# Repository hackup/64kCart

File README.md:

# 64kCart

The 64kCart is a simple bank switching cartridge for the C64/C128. It is a remake of the ["64k-Karte"](http://www.idealine.info/emuecke/index_quereinstieg.htm?/emuecke/hardware/64k_modulkart.htm) created by Hucky which supports EPROM types 2764 up to 27512.

There is also no warranty whatsoever. **USE AT YOUR OWN RISK!**.

See my [blog post](https://www.hackup.net/2019/07/bank-switching-cartridges/) for more details.

## License
[
](http://creativecommons.org/licenses/by-nc-sa/4.0/)

This work is licensed under a
[Creative Commons Attribution-NonCommercial-ShareAlike 4.0 International License](http://creativecommons.org/licenses/by-nc-sa/4.0/).

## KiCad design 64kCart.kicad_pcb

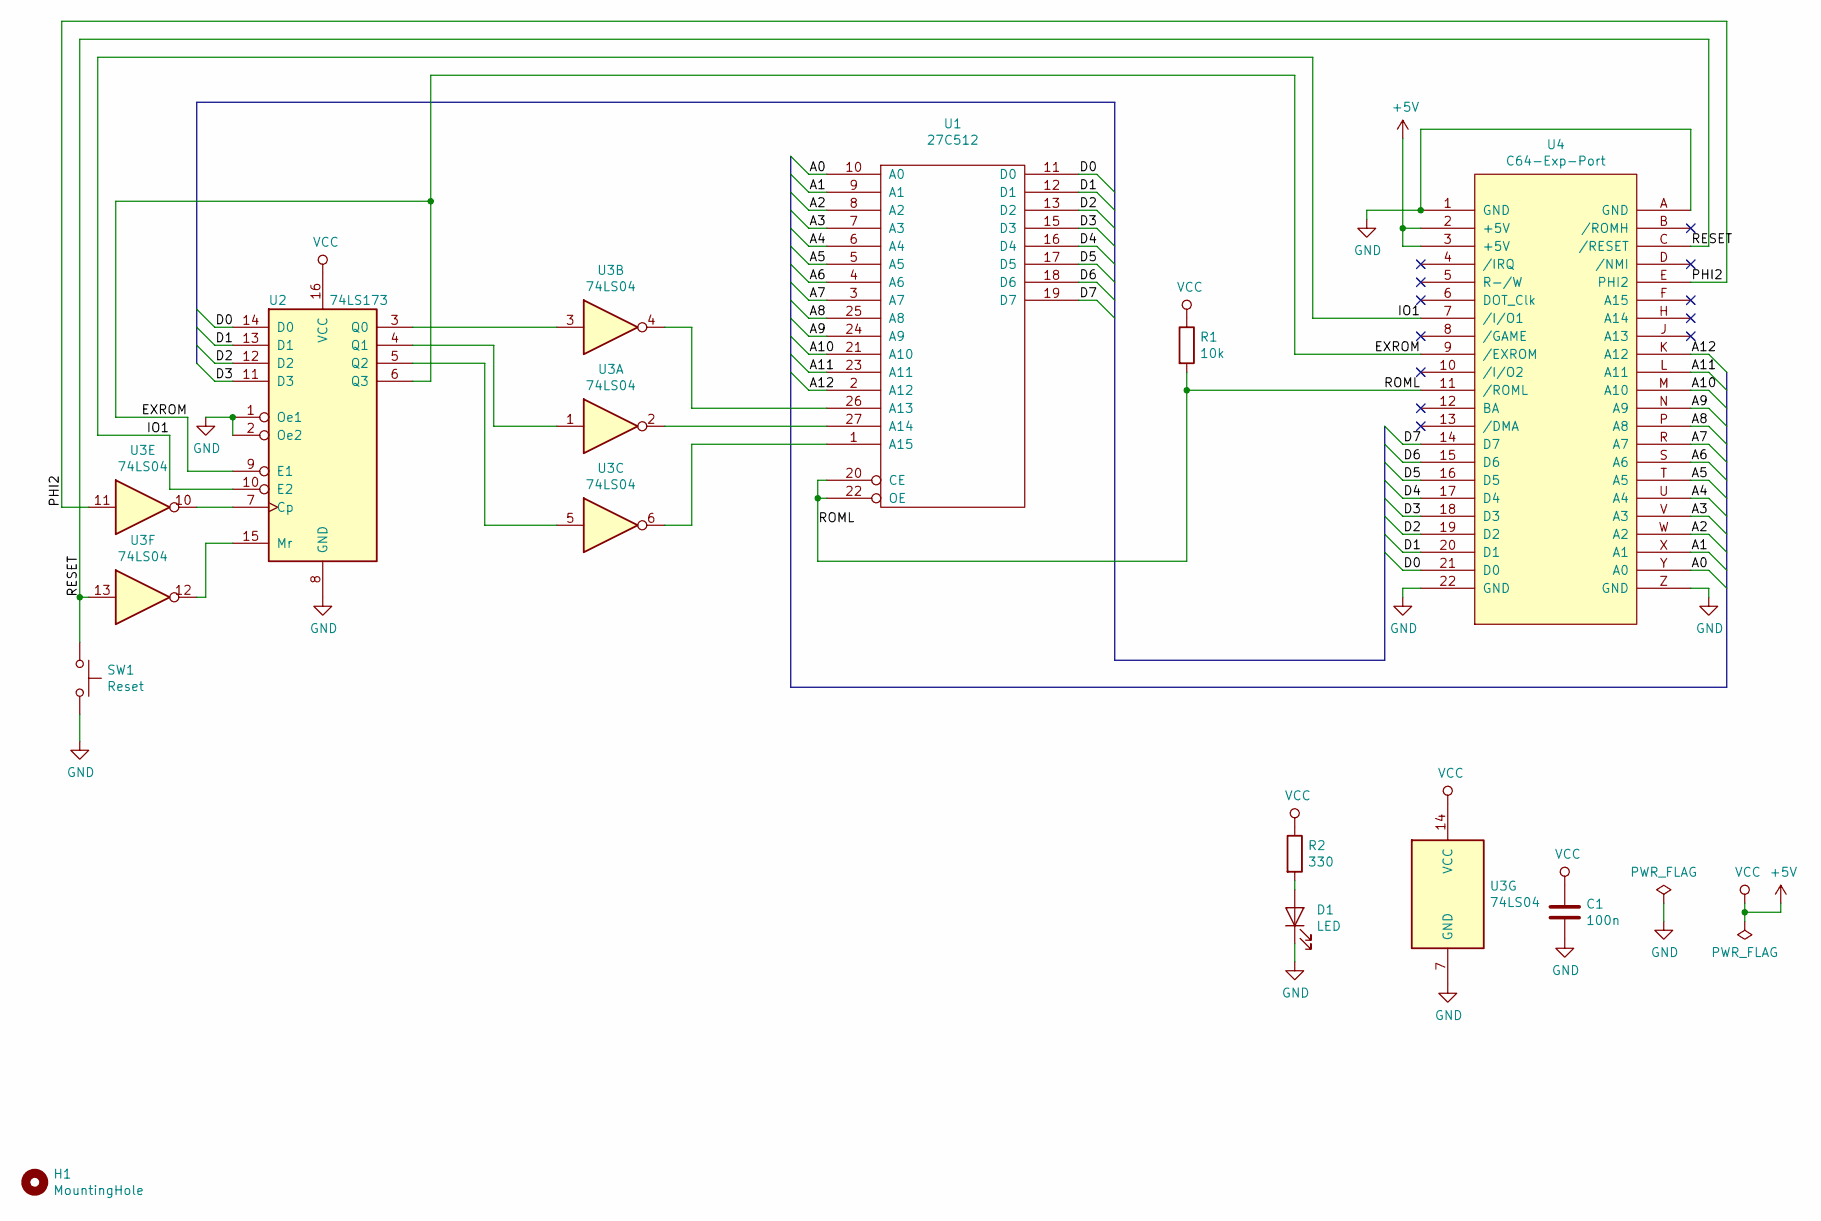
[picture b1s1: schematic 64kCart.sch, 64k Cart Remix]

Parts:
C1: 100n; C_Disc_D4.3mm_W1.9mm_P5.00mm
D1: LED; LED_D3.0mm
H1: MountingHole; MountingHole_CartCombined
R1: 10k; R_Axial_DIN0207_L6.3mm_D2.5mm_P7.62mm_Horizontal
R2: 330; R_Axial_DIN0207_L6.3mm_D2.5mm_P7.62mm_Horizontal
SW1: Reset; SW_Tactile_SPST_Angled_PTS645Vx83-2LFS
U1: 27C512; DIP-28_W15.24mm_Socket
U2: 74LS173; DIP-16_W7.62mm_Socket
U3: 74LS04; DIP-14_W7.62mm_Socket
U4: C64-Exp-Port; C64-Cart-NoSilkS

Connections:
+5V: C1.1, R1.1, R2.1, U1.28 (VCC), U2.16 (VCC), U3.14 (VCC), U4.2 (+5V), U4.3 (+5V)
/A0: U1.10 (A0), U4.Y (A0)
/A1: U1.9 (A1), U4.X (A1)
/A2: U1.8 (A2), U4.W (A2)
/A3: U1.7 (A3), U4.V (A3)
/A4: U1.6 (A4), U4.U (A4)
/A5: U1.5 (A5), U4.T (A5)
/A6: U1.4 (A6), U4.S (A6)
/A7: U1.3 (A7), U4.R (A7)
/A8: U1.25 (A8), U4.P (A8)
/A9: U1.24 (A9), U4.N (A9)
/A10: U1.21 (A10), U4.M (A10)
/A11: U1.23 (A11), U4.L (A11)
/A12: U1.2 (A12), U4.K (A12)
/D0: U1.11 (D0), U2.14 (D0), U4.21 (D0)
/D1: U1.12 (D1), U2.13 (D1), U4.20 (D1)
/D2: U1.13 (D2), U2.12 (D2), U4.19 (D2)
/D3: U1.15 (D3), U2.11 (D3), U4.18 (D3)
/D4: U1.16 (D4), U4.17 (D4)
/D5: U1.17 (D5), U4.16 (D5)
/D6: U1.18 (D6), U4.15 (D6)
/D7: U1.19 (D7), U4.14 (D7)
/EXROM: U2.6 (Q3), U2.9 (E1), U4.9 (/EXROM)
/IO1: U2.10 (E2), U4.7 (/I/O1)
/PHI2: U3.11, U4.E (PHI2)
/RESET: SW1.1, U3.13, U4.C (/RESET)
/ROML: R1.2, U1.20 (CE), U1.22 (OE), U4.11 (/ROML)
GND: C1.2, D1.1 (K), SW1.2, U1.14 (GND), U2.1 (Oe1), U2.2 (Oe2), U2.8 (GND), U3.7 (GND), U4.1 (GND), U4.22 (GND), U4.A (GND), U4.Z (GND)
unnamed: D1.2 (A), R2.2
unnamed: U1.1 (A15), U3.6
unnamed: U1.26 (A13), U3.4
unnamed: U1.27 (A14), U3.2
unnamed: U2.3 (Q0), U3.3
unnamed: U2.4 (Q1), U3.1
unnamed: U2.5 (Q2), U3.5
unnamed: U2.7 (Cp), U3.10
unnamed: U2.15 (Mr), U3.12

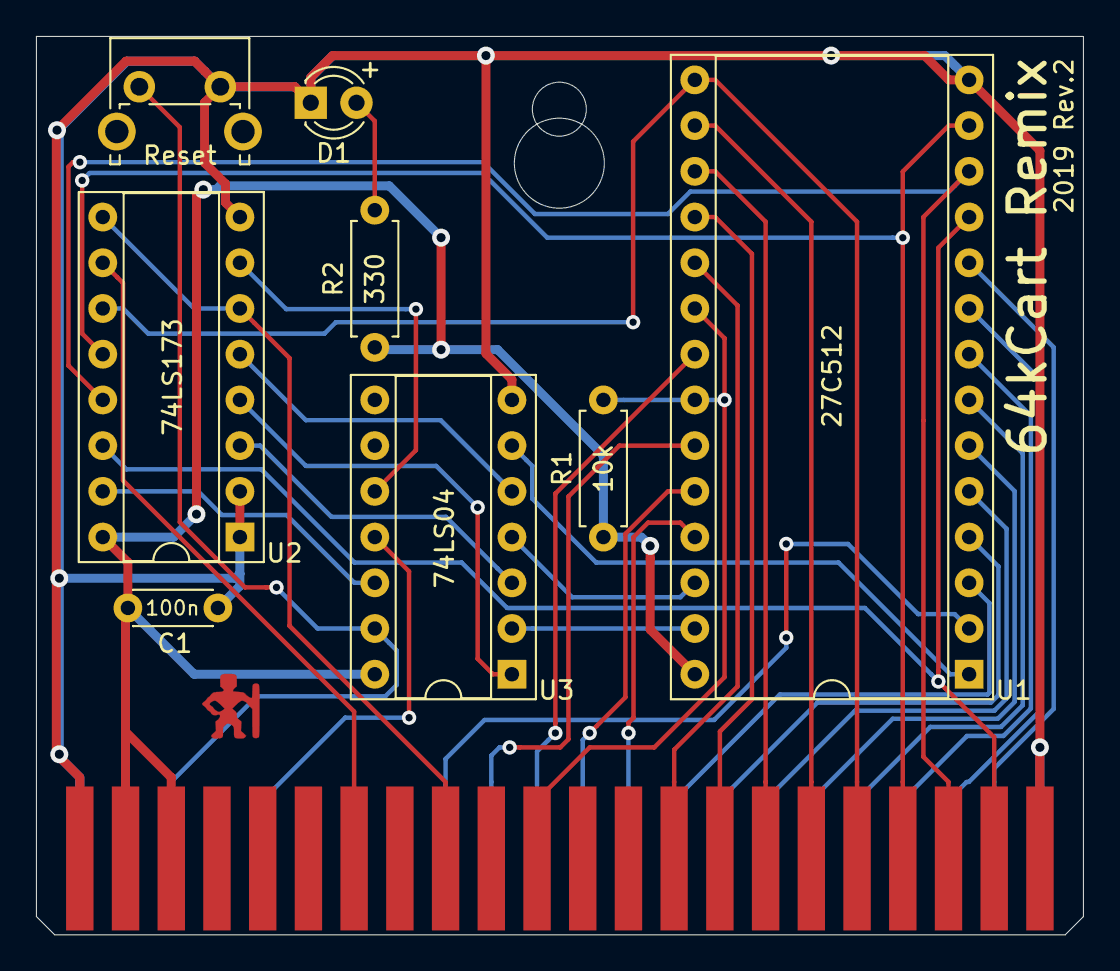
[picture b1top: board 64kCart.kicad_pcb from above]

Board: 2 copper layers, 58.2 x 49.9 mm, 10 parts (0 on the bottom side), 37 nets.

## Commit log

2019-05-05 Initial commit.
2019-05-05 Assigned first footprints.
2019-05-05 Minor improvements.
2019-05-06 Some work on board layout.
2019-05-06 First layout completed.
2019-05-06 First gerber export.
2019-05-07 Mark LED orientation.
2019-07-09 Added readme.
2019-07-09 Fixed media link.
2019-07-11 Updated readme.
2020-12-11 Minor updates for revision 2.
